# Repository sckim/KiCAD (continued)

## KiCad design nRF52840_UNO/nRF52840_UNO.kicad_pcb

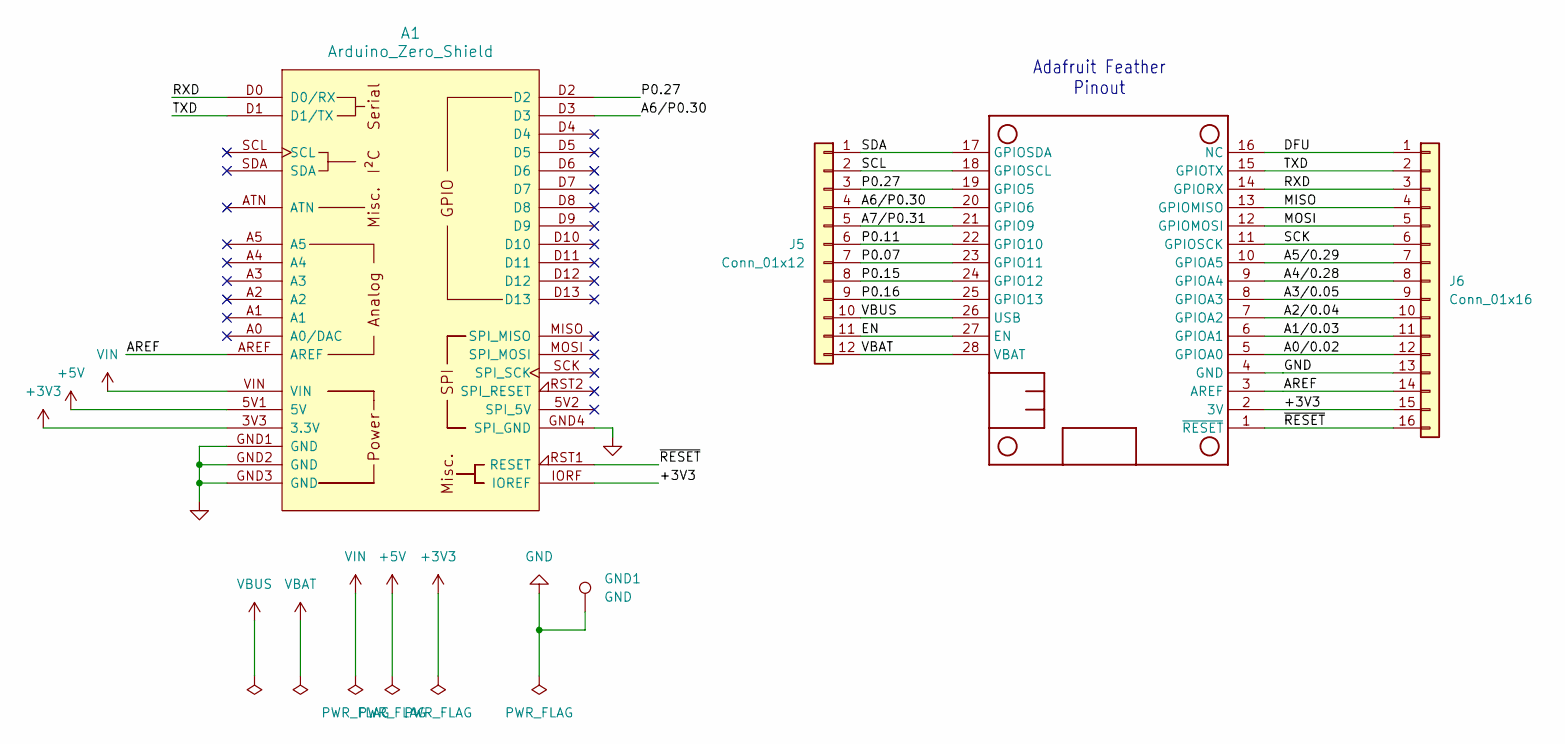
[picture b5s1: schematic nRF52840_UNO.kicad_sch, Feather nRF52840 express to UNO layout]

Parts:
A1: Arduino_Zero_Shield
GND1: GND; PinHeader_1x01_P2.54mm_Vertical
J5: Conn_01x12; PinHeader_1x12_P2.54mm_Vertical
J6: Conn_01x16; PinHeader_1x16_P2.54mm_Vertical
MS1: FEATHERWING_NODIM

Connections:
+3V3: A1.3V3 (3.3V), A1.IORF (IOREF), J6.15, MS1.2 (3V)
+5V: A1.5V1 (5V)
/A0/0.02: J6.12, MS1.5 (GPIOA0)
/A1/0.03: J6.11, MS1.6 (GPIOA1)
/A2/0.04: J6.10, MS1.7 (GPIOA2)
/A3/0.05: J6.9, MS1.8 (GPIOA3)
/A4/0.28: J6.8, MS1.9 (GPIOA4)
/A5/0.29: J6.7, MS1.10 (GPIOA5)
/A7/P0.31: J5.5, MS1.21 (GPIO9)
/AREF: A1.AREF, J6.14, MS1.3 (AREF)
/DFU: J6.1, MS1.16 (NC)
/EN: J5.11, MS1.27 (EN)
/MISO: J6.4, MS1.13 (GPIOMISO)
/MOSI: J6.5, MS1.12 (GPIOMOSI)
/P0.07: J5.7, MS1.23 (GPIO11)
/P0.11: J5.6, MS1.22 (GPIO10)
/P0.15: J5.8, MS1.24 (GPIO12)
/P0.16: J5.9, MS1.25 (GPIO13)
/P0.27: A1.D2, J5.3, MS1.19 (GPIO5)
/RXD: A1.D0 (D0/RX), J6.3, MS1.14 (GPIORX)
/SCK: J6.6, MS1.11 (GPIOSCK)
/SCL: J5.2, MS1.18 (GPIOSCL)
/SDA: J5.1, MS1.17 (GPIOSDA)
/TXD: A1.D1 (D1/TX), J6.2, MS1.15 (GPIOTX)
/~RESET: A1.RST1 (RESET), J6.16, MS1.1 (~RESET)
GND: A1.GND1 (GND), A1.GND2 (GND), A1.GND3 (GND), A1.GND4 (SPI_GND), GND1.1, J6.13, MS1.4 (GND)
VBAT: J5.12, MS1.28 (VBAT)
VBUS: J5.10, MS1.26 (USB)
VIN: A1.VIN

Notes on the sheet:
Adafruit Feather Pinout

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
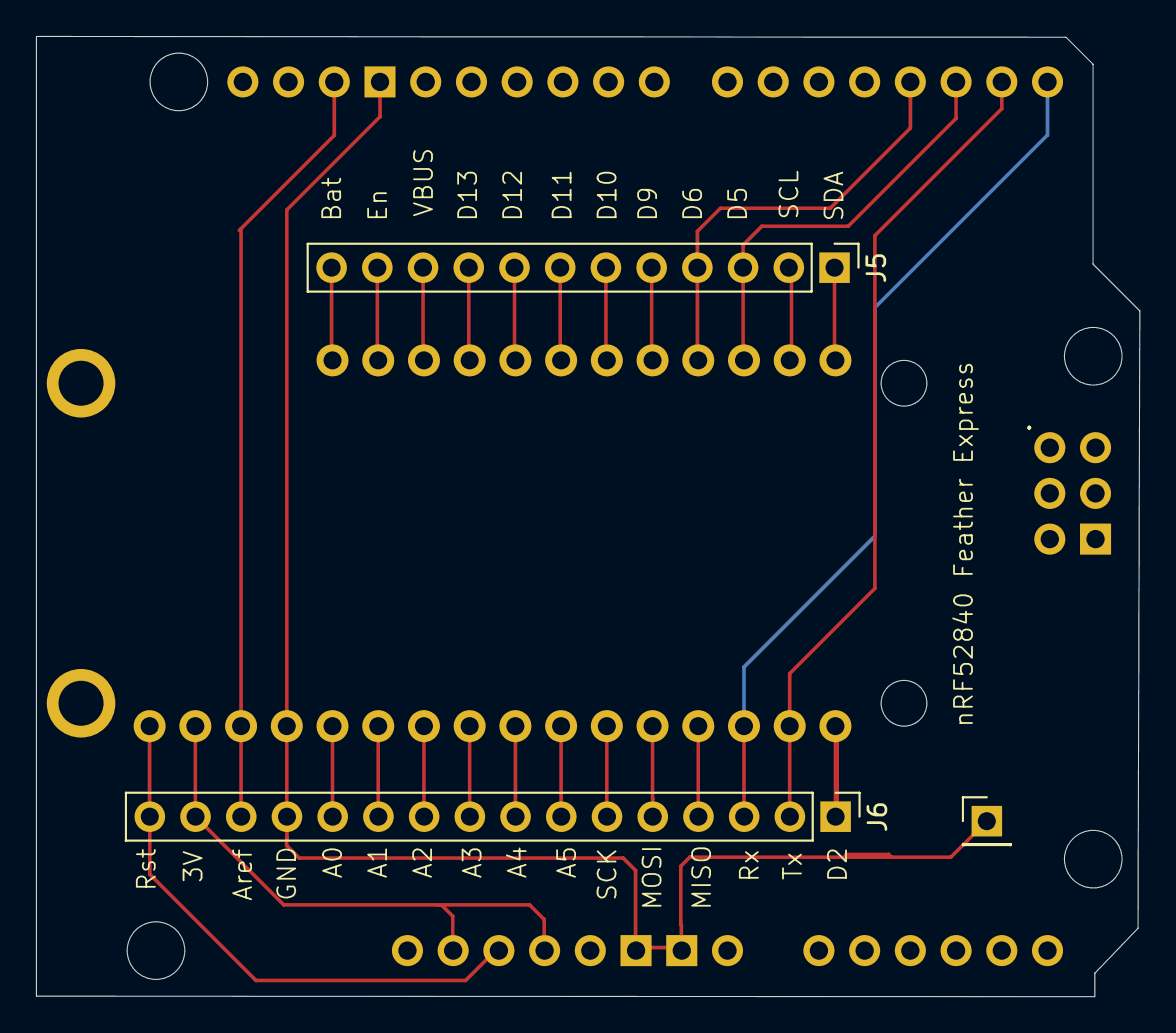
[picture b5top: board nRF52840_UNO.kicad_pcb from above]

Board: 2 copper layers, 61.3 x 53.3 mm, 5 parts (0 on the bottom side), 28 nets.

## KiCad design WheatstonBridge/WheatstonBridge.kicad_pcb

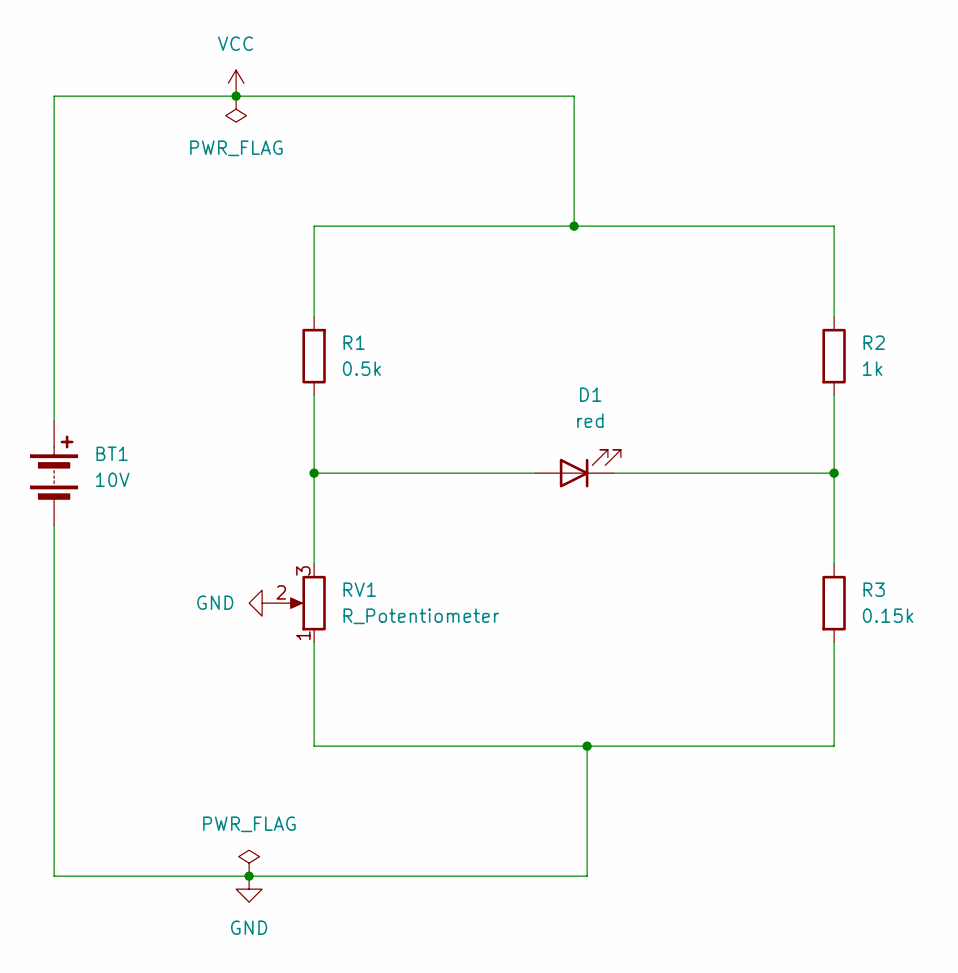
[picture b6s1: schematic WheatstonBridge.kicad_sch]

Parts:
BT1: 10V; BatteryHolder_Keystone_1060_1x2032
D1: red; LED_D5.0mm
R1: 0.5k; R_Axial_DIN0309_L9.0mm_D3.2mm_P12.70mm_Horizontal
R2: 1k; R_Axial_DIN0309_L9.0mm_D3.2mm_P12.70mm_Horizontal
R3: 0.15k; R_Axial_DIN0309_L9.0mm_D3.2mm_P12.70mm_Horizontal
RV1: R_Potentiometer; Potentiometer_Bourns_3296W_Vertical

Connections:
GND: BT1.2 (-), R3.2, RV1.1, RV1.2
unnamed: D1.2 (A), R1.1, RV1.3
unnamed: D1.1 (K), R2.2, R3.1
VCC: BT1.1 (+), R1.2, R2.1

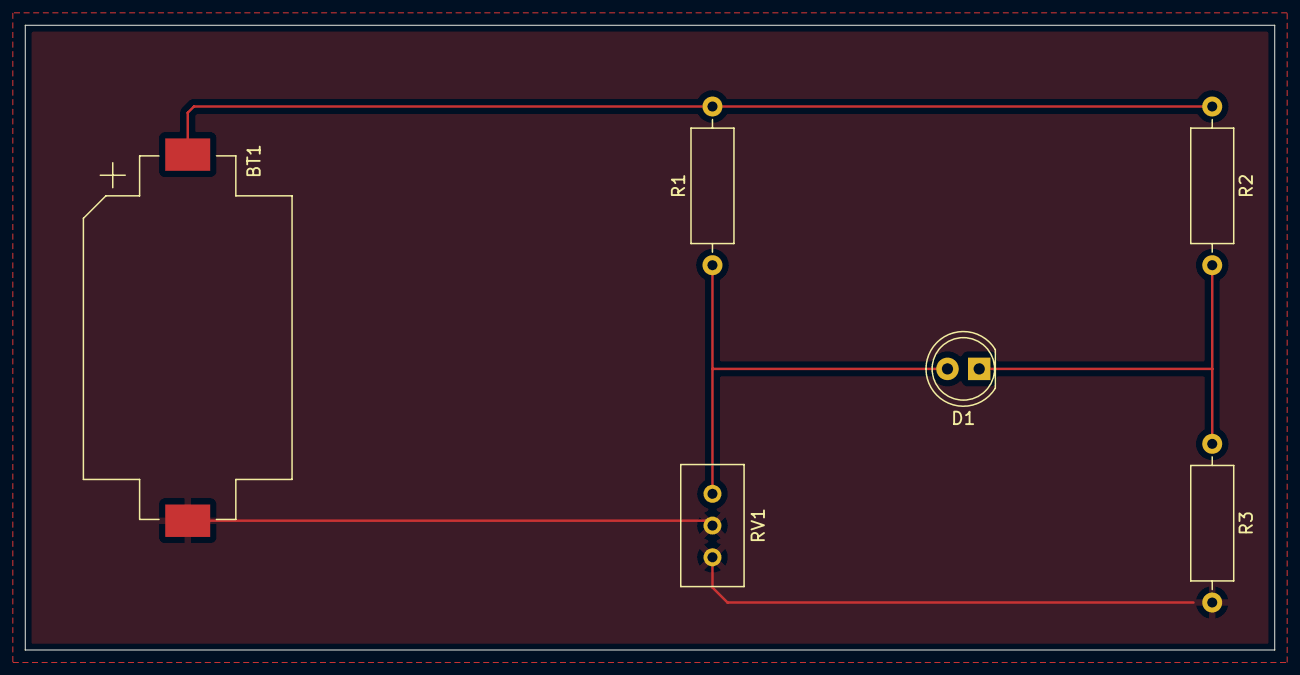
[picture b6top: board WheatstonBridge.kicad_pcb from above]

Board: 2 copper layers, 100.0 x 50.0 mm, 6 parts (0 on the bottom side), 4 nets.

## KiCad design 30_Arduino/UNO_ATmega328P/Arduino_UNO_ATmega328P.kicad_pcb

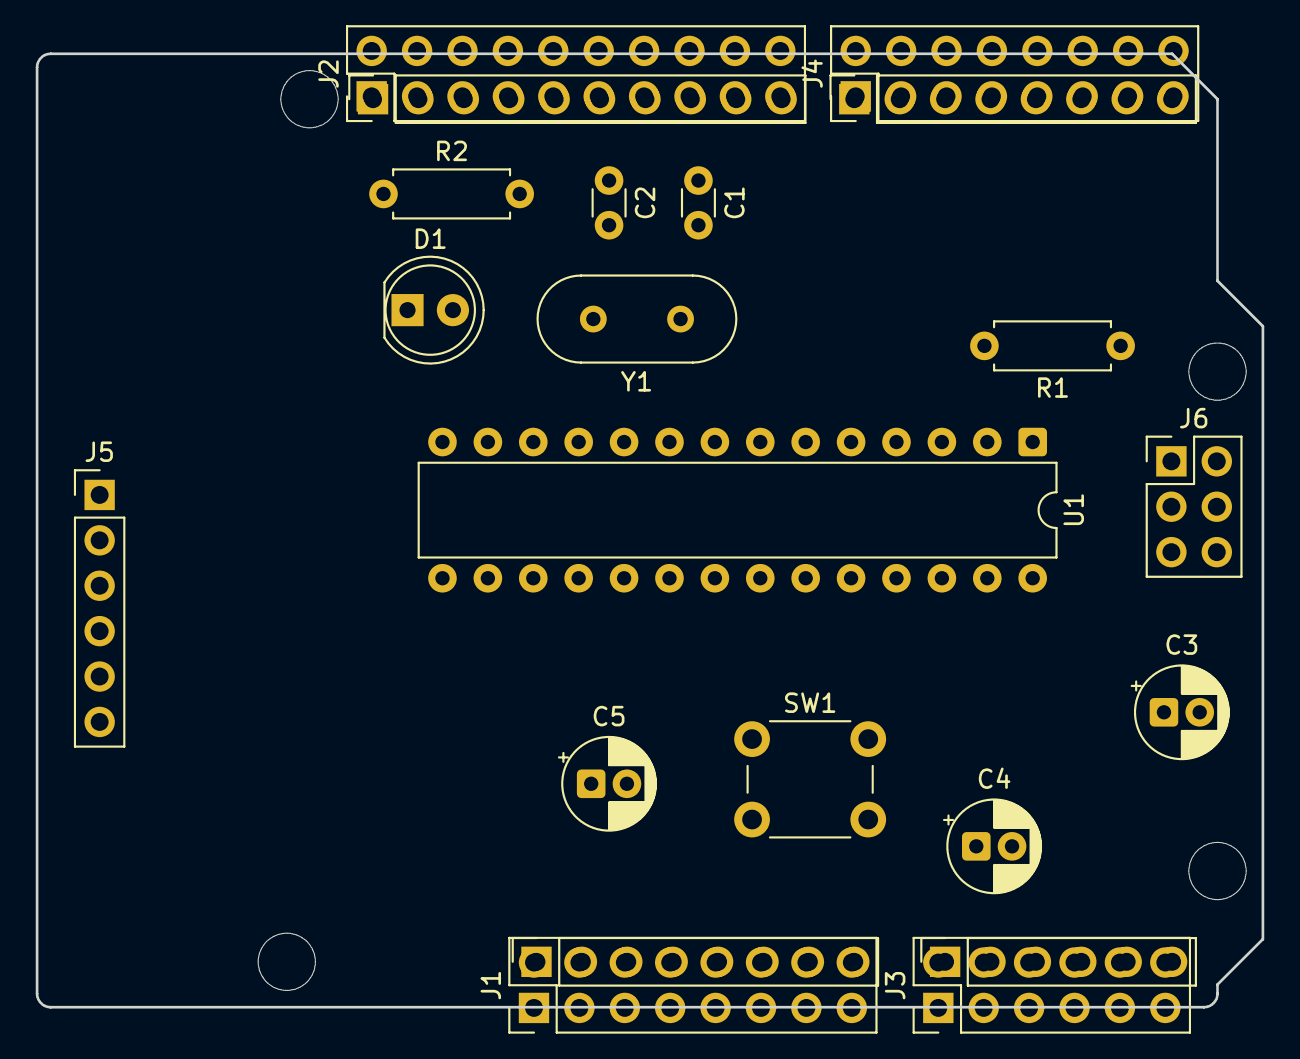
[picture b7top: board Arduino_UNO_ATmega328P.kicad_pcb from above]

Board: 2 copper layers, 68.6 x 53.3 mm, 25 parts (0 on the bottom side), 28 nets, no tracks yet.

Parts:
C1, C2: 22pF; C_Disc_D3.0mm_W1.6mm_P2.50mm
C3: C; CP_Radial_D5.0mm_P2.00mm
C4, C5: 0.1uF; CP_Radial_D5.0mm_P2.00mm
D1: LED; LED_D5.0mm
J1: Power; PinSocket_1x08_P2.54mm_Vertical
J1#2: Power; PinHeader_2x08_P2.54mm_Vertical
J2: Digital/PWM; PinSocket_1x10_P2.54mm_Vertical
J2#2: Digital/PWM; PinHeader_2x10_P2.54mm_Vertical
J3: Analog; PinSocket_1x06_P2.54mm_Vertical
J3#2: Analog; PinHeader_2x06_P2.54mm_Vertical
J4: Digital/PWM; PinSocket_1x08_P2.54mm_Vertical
J4#2: Digital/PWM; PinHeader_2x08_P2.54mm_Vertical
J5: Conn_01x06; PinHeader_1x06_P2.54mm_Vertical
J6: Conn_02x03_Odd_Even; PinHeader_2x03_P2.54mm_Vertical
MH1, MH2, MH3, MH4: MountingHole_3.2mm
R1: 10K; R_Axial_DIN0207_L6.3mm_D2.5mm_P7.62mm_Horizontal
R2: 330; R_Axial_DIN0207_L6.3mm_D2.5mm_P7.62mm_Horizontal
SW1: SW_Push; SW_PUSH_6mm
U1: ATmega328P-P; DIP-28_W7.62mm
Y1: 16MHz; Crystal_HC49-U_Vertical

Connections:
/2: J4.6, U1.4 (PD2)
/4: J4.4, U1.6 (PD4)
/7: J4.1, U1.13 (PD7)
/8: J2.10, U1.14 (PB0)
/12: J2.6, J6.1, U1.18 (PB4)
/13: J2.5, J6.3, R2.2, U1.19 (PB5)
/*3: J4.5, U1.5 (PD3)
/*5: J4.3, U1.11 (PD5)
/*6: J4.2, U1.12 (PD6)
/*9: J2.9, U1.15 (PB1)
/*10: J2.8, U1.16 (PB2)
/*11: J2.7, J6.4, U1.17 (PB3)
/A0: J3.1, U1.23 (PC0)
/A1: J3.2, U1.24 (PC1)
/A2: J3.3, U1.25 (PC2)
/A3: J3.4, U1.26 (PC3)
/AREF: C5.1, J2.3, U1.21 (AREF)
/RTS: C3.1, J5.6
/RX/0: J4.8, J5.4, U1.2 (PD0)
/SCL/A5: J2.1, J3.6, U1.28 (PC5)
/SDA/A4: J2.2, J3.5, U1.27 (PC4)
/TX/1: J4.7, J5.5, U1.3 (PD1)
/~RESET: C3.2, J1.3, J6.5, R1.2, SW1.1, U1.1 (~RESET/PC6)
GND: C1.1, C2.1, C4.2, C5.2, D1.1 (K), J1.6, J1.7, J2.4, J5.1, J5.2, J6.6, SW1.2, U1.8 (GND), U1.22 (GND)
unnamed: D1.2 (A), R2.1
unnamed: C1.2, U1.9 (XTAL1/PB6), Y1.1
unnamed: C2.2, U1.10 (XTAL2/PB7), Y1.2
VCC: C4.1, J1.8, J5.3, J6.2, R1.1, U1.7 (VCC), U1.20 (AVCC)

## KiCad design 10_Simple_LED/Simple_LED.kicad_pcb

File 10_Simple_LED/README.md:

# 예제 1. Simple LED — 회로도에서 PCB까지

코인 전지로 LED 하나를 켜는 가장 간단한 회로이다.
부품은 3개뿐이지만 **회로도 작성 → 풋프린트 지정 → PCB 배치·배선 → 제작 파일(거버) 출력**까지 KiCad의 전체 흐름을 한 번에 경험할 수 있다.

<table>
    <tr>
        <td></td>
        <td></td>
    </tr>
</table>

> KiCad 10을 기준으로 설명한다. KiCad를 처음 쓴다면 [Docs](../Docs/)의 *Getting Started in KiCad*를 함께 보면 좋다.

---

## 1. 폴더 구성

| 파일 | 설명 |
|---|---|
| `Simple_LED.kicad_pro` | 프로젝트 파일이다. **이 파일을 열면** 회로도와 PCB를 모두 다룰 수 있다. |
| `Simple_LED.kicad_sch` | 회로도 |
| `Simple_LED.kicad_pcb` | PCB 레이아웃 |
| `gerber/` | PCB 제작 업체에 보내는 제작 파일(거버, 드릴) |
| `Simple_LED-backups/`, `*.kicad_prl`, `fp-info-cache` | KiCad가 자동으로 만드는 백업/설정/캐시 파일이다. 신경 쓰지 않아도 된다. |

## 2. 회로 이해하기

전지(+) → 저항 → LED → 전지(−) 순서로 전류가 흐른다. 저항은 LED에 흐르는 전류를 제한한다.

| 참조 번호 | 부품 | 심볼 | 풋프린트 |
|---|---|---|---|
| BT1 | CR2032 코인 전지 (3 V) | `Device:Battery_Cell` | `Battery:BatteryHolder_Keystone_1058_1x2032` |
| R1 | 저항 | `Device:R` | `Resistor_THT:R_Axial_DIN0309_L9.0mm_D3.2mm_P12.70mm_Horizontal` |
| D1 | 5 mm LED | `Device:LED` | `LED_THT:LED_D5.0mm` |

회로도에는 부품 외에 다음 요소도 쓰였다.
- **전원 심볼** `VCC`, `GND`: 이름이 같은 전원 심볼끼리는 선을 그리지 않아도 연결된다.
- **넷 레이블** `led`: 저항과 LED 사이 연결선에 붙인 이름이다. PCB에서 이 이름(`/led`)으로 연결을 확인할 수 있다.
- **PWR_FLAG** 2개: "이 넷에 전원이 공급된다"는 사실을 ERC(전기 규칙 검사)에 알려 준다. 없으면 ERC가 *Input Power pin not driven* 오류를 낸다.

### 저항값 정하기
예제 파일의 R1 값은 `R`로 비어 있다. 직접 계산해서 넣어 본다.

```
R = (전지 전압 − LED 순방향 전압) / LED 전류
  = (3 V − 2 V) / 10 mA
  = 100 Ω
```

빨간 LED의 순방향 전압은 약 2 V이다. CR2032는 큰 전류를 오래 내지 못하므로 **100 Ω ~ 330 Ω** 사이가 적당하다.

---

## 3. 예제 열어 보기

1. KiCad를 실행하고 **File → Open Project**에서 `Simple_LED.kicad_pro`를 연다.
2. 프로젝트 창에서 **Schematic Editor**(회로도)와 **PCB Editor**(PCB)를 각각 열어 본다.
3. PCB 편집기에서 **View → 3D Viewer** (`Alt+3`)로 완성된 보드를 입체로 확인한다.

> 예제 파일은 KiCad 8에서 만들어졌다. KiCad 10에서 열면 형식 변환 안내가 나오는데, 그대로 진행하면 된다. 저장하면 KiCad 10 형식으로 바뀌어 **KiCad 8에서는 다시 열 수 없다.**

---

## 4. 처음부터 직접 만들어 보기

예제를 보기만 하는 것보다 직접 한 번 만들어 보는 편이 훨씬 빨리 익혀진다. 아래 순서에 따라 새 프로젝트로 똑같은 보드를 만들어 본다.

### 4-1. 새 프로젝트 만들기
1. **File → New Project** 를 선택하고, 새 폴더에 `My_LED` 같은 이름으로 저장한다.
2. 프로젝트 창에 `.kicad_pro`, `.kicad_sch`, `.kicad_pcb` 파일이 만들어졌는지 확인한다.

### 4-2. 회로도 그리기 (Schematic Editor)
자주 쓰는 단축키: `A` 심볼 추가, `P` 전원 심볼 추가, `W` 배선, `L` 넷 레이블, `M` 이동, `G` 끌기(연결 유지), `R` 회전, `E` 속성 편집, `Del` 삭제, `Esc` 취소

1. **부품 배치** — `A`를 누르고 검색창에 `Battery_Cell`, `R`, `LED`를 차례로 검색해 배치한다.
2. **전원 심볼 배치** — `P`를 누르고 `VCC`와 `GND`를 배치한다. `PWR_FLAG`도 2개 배치한다.
3. **배선** — `W`를 누르고 핀 끝(작은 원)을 클릭해 선을 그린다. 연결이 끝나면 더블클릭하거나 `Esc`를 누른다.
   - 전지(+) → `VCC`, 전지(−) → `GND`
   - `VCC` → 저항 한쪽, 저항 다른 쪽 → LED 애노드(A, 삼각형 쪽)
   - LED 캐소드(K, 막대 쪽) → `GND`
   - `PWR_FLAG` 하나는 `VCC`에, 다른 하나는 `GND`에 연결
4. **넷 레이블** — 저항과 LED 사이 선 위에서 `L`을 누르고 `led`를 입력해 붙인다.
5. **값 입력** — 저항 위에서 `E`를 눌러 Value를 `100`처럼 계산한 값으로 바꾼다.
6. **부품 번호 매기기** — **Tools → Annotate Schematic** 을 실행하면 `R?`에 `R1`처럼 번호가 붙는다.
7. **전기 규칙 검사(ERC)** — **Inspect → Electrical Rules Checker** 를 실행한다. 오류가 0개가 될 때까지 고친다.
   - 핀이 연결되지 않았다는 오류: 선 끝이 핀 끝에 정확히 닿았는지 확인한다.
   - *Input Power pin not driven*: `PWR_FLAG`가 빠지지 않았는지 확인한다.

### 4-3. 풋프린트 지정
회로도 심볼은 부품의 "기능"을, 풋프린트는 부품이 PCB에 놓일 "실제 모양(패드 위치와 크기)"을 나타낸다.

1. **Tools → Assign Footprints** 를 연다.
2. 왼쪽 목록에서 라이브러리를 고르고, 오른쪽 목록에서 풋프린트를 더블클릭해 지정한다. 위 [2장 표](#2-회로-이해하기)의 풋프린트를 그대로 쓰면 된다.
3. **OK**를 누르고 회로도를 저장한다.

> 풋프린트를 고를 때는 **실제로 구입할 부품의 데이터시트** 치수와 맞는지 확인하는 습관을 들인다.

### 4-4. PCB로 넘기기 (PCB Editor)
자주 쓰는 단축키: `M` 이동, `R` 회전, `F` 앞/뒷면 뒤집기, `X` 배선, `V` 배선 중 비아 추가, `D` 배선 끌기, `B` 동박 영역 채우기, `Del` 삭제

1. PCB 편집기를 열고 **Tools → Update PCB from Schematic** (`F8`) 을 실행한 뒤 **Update PCB** 를 누른다. 부품들이 커서에 붙어 나오면 빈 곳을 클릭해 내려놓는다.
2. 부품 사이의 가는 선(**래츠네스트, ratsnest**)은 연결해야 할 곳을 보여 준다.

### 4-5. 보드 외곽선 그리기
1. 오른쪽 **Layers** 창에서 `Edge.Cuts` 레이어를 선택한다.
2. **Place → Draw Rectangle** 로 부품을 모두 감싸는 사각형을 그린다. 예제는 **50 mm × 50 mm** 이다.
3. 정확한 크기가 필요하면 사각형을 더블클릭해 좌표를 직접 입력한다.

### 4-6. 부품 배치
1. `M`으로 부품을 옮기고 `R`로 회전해, 래츠네스트가 서로 꼬이지 않게 배치한다.
2. 예제에서는 **전지 홀더(BT1)를 보드 뒷면**에 두었다. BT1을 선택하고 `F`를 누르면 뒷면(B.Cu)으로 뒤집힌다.
3. LED의 극성 표시(평평한 면 = 캐소드)가 실크스크린에 보이는지 확인한다.

### 4-7. 배선
1. 오른쪽 위 레이어 선택에서 `F.Cu`(앞면 동박)를 고르고, 패드 위에서 `X`를 눌러 래츠네스트를 따라 배선한다.
2. 배선 중에 `V`를 누르면 **비아**가 생기고, 반대 면(`B.Cu`)으로 이어서 배선할 수 있다.
3. 예제의 설계 규칙은 **배선 폭 0.2 mm, 간격 0.2 mm, 비아 0.6 mm / 드릴 0.3 mm** 이다. **File → Board Setup → Design Rules** 에서 확인하고 바꿀 수 있다.
   - LED 정도의 작은 전류에는 0.2 mm로 충분하다. 손으로 납땜할 보드라면 0.4 mm 이상으로 넓혀도 좋다.

### 4-8. GND 동박 영역(Copper Zone)
넓은 GND 면을 만들면 GND 배선을 따로 그리지 않아도 되고, 노이즈에도 유리하다.

1. **Place → Add Filled Zone** 을 선택하고 보드 외곽을 따라 클릭한다.
2. 창이 뜨면 레이어는 `B.Cu`, 넷은 `GND`를 고른다.
3. `B`를 눌러 영역을 채운다. GND 래츠네스트가 사라지면 연결된 것이다.

### 4-9. 설계 규칙 검사(DRC)와 3D 확인
1. **Inspect → Design Rules Checker** 에서 **Run DRC** 를 누른다.
2. **Unconnected Items가 0개**이고 오류가 0개인지 확인한다. 오류를 클릭하면 PCB에서 해당 위치로 이동한다.
3. **View → 3D Viewer** (`Alt+3`)로 부품이 제자리에 있는지, 뒷면의 전지 홀더가 잘 보이는지 확인한다.

### 4-10. 제작 파일(거버) 출력
1. **File → Fabrication Outputs → Gerbers (.gbr)** 를 연다.
2. 출력 폴더를 `gerber/`로 지정하고, 다음 레이어가 선택되어 있는지 확인한 뒤 **Plot** 을 누른다.
   `F.Cu`, `B.Cu`, `F.Silkscreen`, `B.Silkscreen`, `F.Mask`, `B.Mask`, `Edge.Cuts` (SMD 부품이 있으면 `F.Paste`, `B.Paste`도 포함)
3. 같은 창에서 **Generate Drill Files…** 를 눌러 드릴 파일(`.drl`)도 만든다.
4. 프로젝트 창의 **Gerber Viewer** 로 `gerber/` 폴더의 파일을 열어 모양이 맞는지 확인한다.
5. `gerber/` 폴더를 압축(zip)하면 PCB 제작 업체에 주문할 수 있다.

---

## 5. 자주 하는 실수

| 증상 | 원인과 해결 |
|---|---|
| 선을 그렸는데 ERC에서 연결되지 않았다고 나옴 | 선 끝이 핀 끝(작은 원)에 닿지 않았다. `G`로 끌어서 다시 붙인다. |
| `Input Power pin not driven` 오류 | `PWR_FLAG`를 `VCC`와 `GND`에 연결한다. |
| PCB에 부품이 나타나지 않음 | 회로도에서 풋프린트를 지정하지 않았다. 4-3을 다시 하고 `F8`을 실행한다. |
| 회로도를 고쳤는데 PCB에 반영되지 않음 | 회로도를 수정한 뒤에는 **항상 `F8`(Update PCB from Schematic)** 을 다시 실행한다. |
| 실제 보드에서 LED가 켜지지 않음 | LED 방향이 반대이다. 긴 다리(애노드)가 저항 쪽, 짧은 다리/평평한 면(캐소드)이 GND 쪽이다. |
| 동박 영역이 비어 보임 | `B`를 눌러 영역을 다시 채운다. |

## 6. 다음 단계
- [20_WheatstoneBridge](../20_WheatstoneBridge/): 시뮬레이션이 포함된 두 번째 PCB 예제
- [Docs](../Docs/): KiCad 공식 설명서 (회로도 편집기, PCB 편집기 매뉴얼)

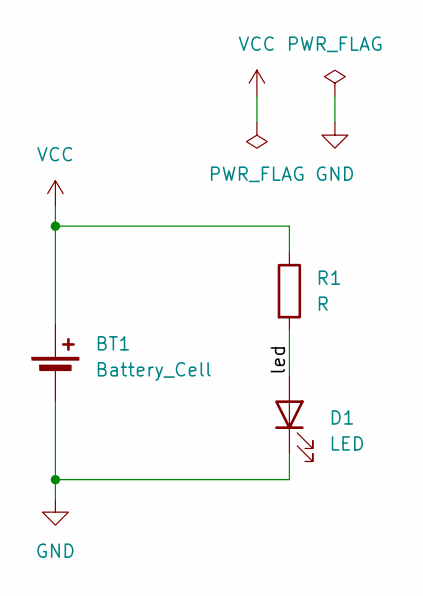
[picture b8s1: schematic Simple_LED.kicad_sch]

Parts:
BT1: Battery_Cell; BatteryHolder_Keystone_1058_1x2032
D1: LED; LED_D5.0mm
R1: R; R_Axial_DIN0309_L9.0mm_D3.2mm_P12.70mm_Horizontal

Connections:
/led: D1.2 (A), R1.2
GND: BT1.2 (-), D1.1 (K)
VCC: BT1.1 (+), R1.1

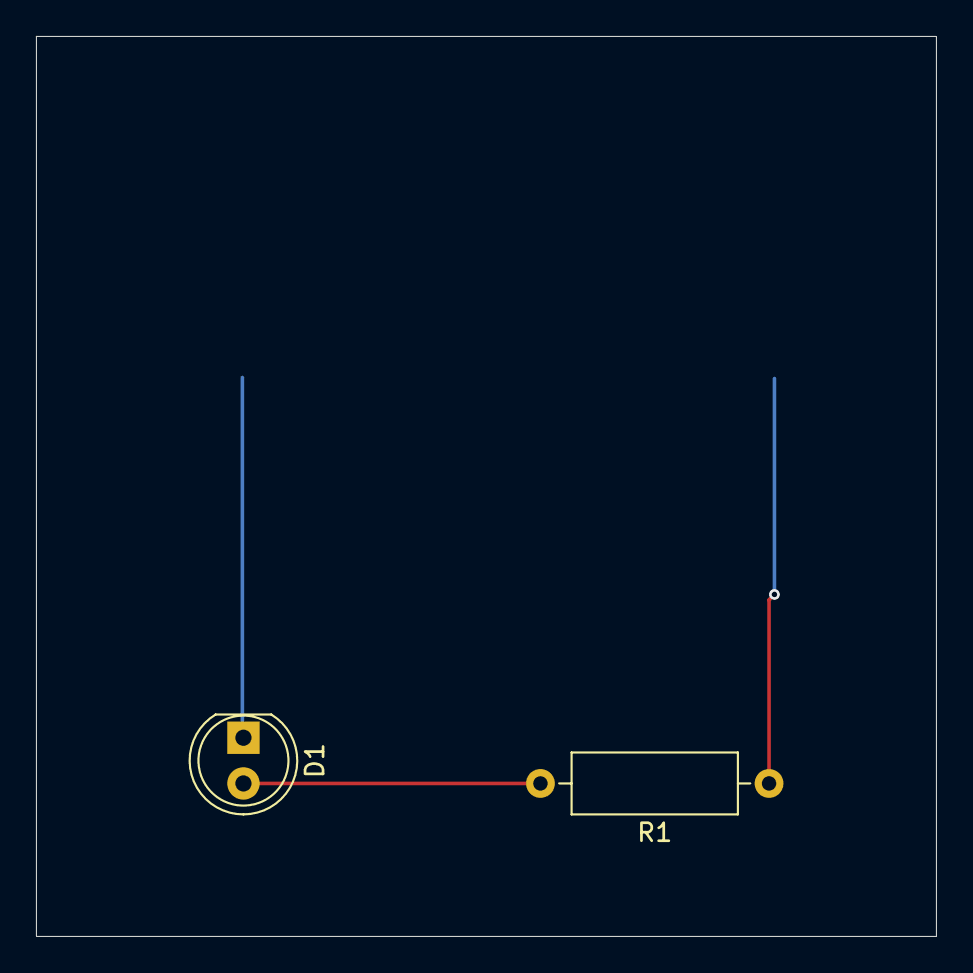
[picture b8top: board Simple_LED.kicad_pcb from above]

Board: 2 copper layers, 50.0 x 50.0 mm, 3 parts (1 on the bottom side), 3 nets.

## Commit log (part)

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2025-01-07 Add examples
2025-01-07 Add WheatstoneBridge
2025-01-07 Add adafruit nRF52
2025-01-07 Add a video
2025-01-07 Add images
2025-01-14 Add 4bits adder
2025-01-14 Update wheatstonebridges
2025-02-12 Add AD2&UNO interface
